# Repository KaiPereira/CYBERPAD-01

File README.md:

# CYBERPAD-01 - Cyberpunk Inspired Macropad

The CYBERPAD-01 is a cyberpunk inspired macropad with 3 keys, a rotary encoder, and a whole lotta silkscreen and neopixels. It uses KMK firmware and was meant to serve as a learning opportunity for PCB's, CAD and rendering. 
## Custom Features
- Custom lasercut acrylic top panel
- EC11 Rotary Encoder for anything really
- 3 Keys to program to your heart's content
- 14 SK6812 MINI-E LEDs for backlight and and diffusion
- Cyberpunk inspired case for maximum aesthetic
-  Exposed PCB design with custom silkscreen cuz it's sick
## CAD Design

I used Onshape to design all of my parts. The laser cut acrylic panel is held together using minimalist bolts and spacers attached to the top plate. The actual case is designed so that everything can fit together seamlessly without using any screws or bolts for minimalism and aesthetics while still being secure.

It comprises of 4 separate 3D printed parts though, the bottom plate/aesthetic walls, the walls, and the top plate, the rotary encoder knob, with the 5th part being the laser cut acrylic top panel, so it's a bit difficult to print, but manageable. [Onshape Link](https://cad.onshape.com/documents/183c405de5c750134bf8a1de/w/282fa5c96ffeba0ae16f58ec/e/f98acd70bf74a51e29d61d0d?renderMode=0&uiState=6869deede1723828ff557213)
## PCB Design

The PCB was designed using KiCad and then I used Figma and the KiCad image converter for creating the silkscreen layers. I actually imported the case design into KiCad so I could use it as reference for the silkscreen which turned out really well.

## Firmware

The CYBERPAD-01 uses KMK firmware (written in Python) and was relatively straightforward.
- The rotary encoder changes volume
- The keys just act as VIM macro's
- Neopixels to backlight and diffuse any color you want

I'll probably make it a bit more complicated in the future, but I think it's kind of handy to have a macropad for some really complicated VIM stuff.

## Bill of Materials (BOM)

Here's everything you'll need to build the CYBERPAD-01:
- 3x Cherry MX Switches
- 3x Keycaps of your choice (I would personally suggest black ones)
- 14x SK6812 MINI-E LEDs
- 1x EC11 Rotary Encoder
- 1x Seeed XIAO RP2040
- 8x M2 Nut and Bolt, 1.5cm, Low profile top
- 8x M2 Spacers, 3mm diameter, 0.6cm, circular, non-threaded
- 1 Case (3 printed parts)
- 1 Custom Laser Cut Acrylic Panel

## Credits and Help

Thanks to @qcoral and @acornitum for starting highway and reviewing projects. @M0HID and @jamdotjar for helping me with Blender and @cheyao for the firmware starter code and helping me make my first macropad!

Also, thanks so much to [PCBWay](https://www.pcbway.com/) for sponsoring the yellow silkscreen PCB's, they look absolutely amazing and I'd highly suggest checking them out if you need really cool looking PCB's and fast turnaround!

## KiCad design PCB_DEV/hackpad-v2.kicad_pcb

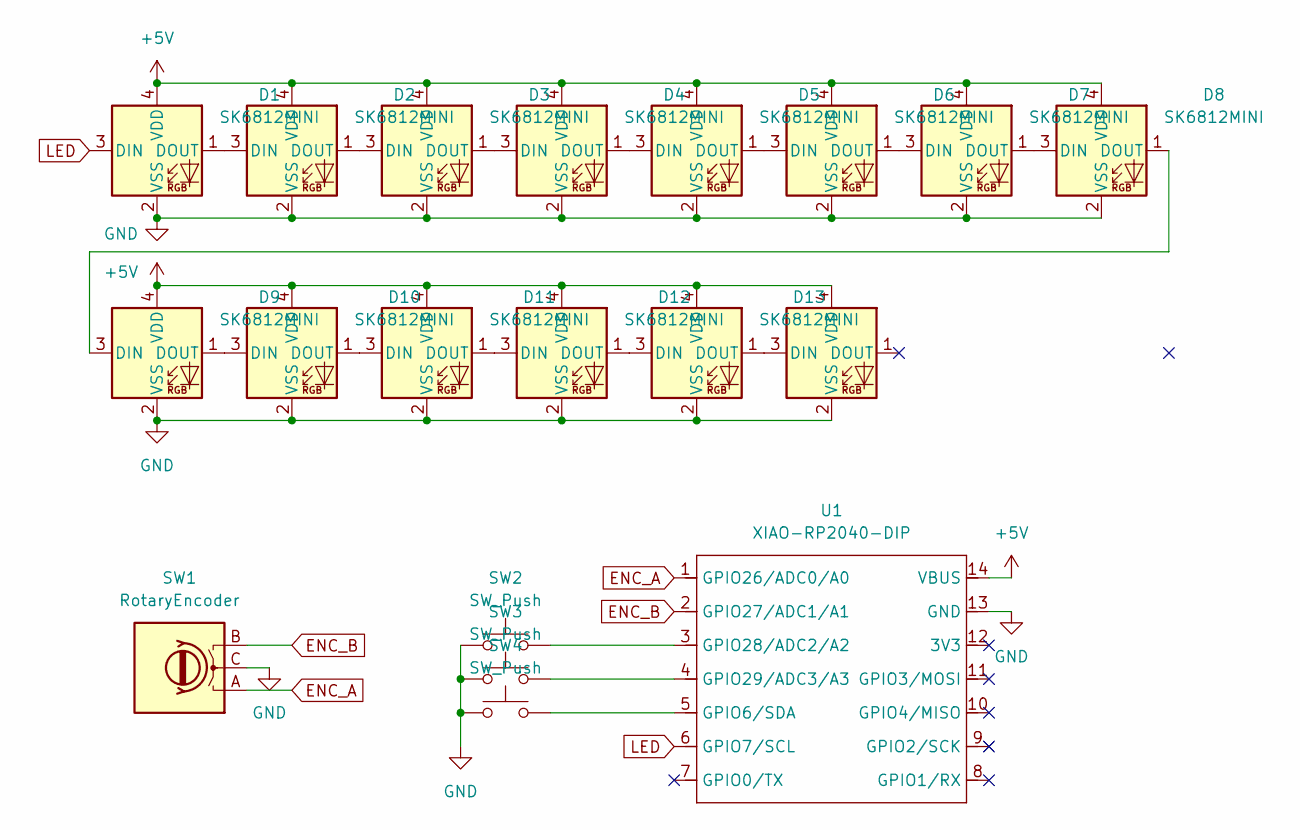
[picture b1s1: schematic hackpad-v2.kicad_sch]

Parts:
D1, D2, D3, D4, D5, D6, D7, D8, D9, D10, D11, D12, D13, D14: SK6812MINI; LED_SK6812MINI_PLCC4_3.5x3.5mm_P1.75mm
SW1: RotaryEncoder; RotaryEncoder_Alps_EC11E-Switch_Vertical_H20mm
SW2, SW3, SW4: SW_Push; SW_Cherry_MX_1.00u_PCB
U1: XIAO-RP2040-DIP

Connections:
+5V: D1.4 (VDD), D2.4 (VDD), D3.4 (VDD), D4.4 (VDD), D5.4 (VDD), D6.4 (VDD), D7.4 (VDD), D8.4 (VDD), D9.4 (VDD), D10.4 (VDD), D11.4 (VDD), D12.4 (VDD), D13.4 (VDD), D14.4 (VDD), U1.14 (VBUS)
ENC_A: SW1.A, U1.1 (GPIO26/ADC0/A0)
ENC_B: SW1.B, U1.2 (GPIO27/ADC1/A1)
GND: D1.2 (VSS), D2.2 (VSS), D3.2 (VSS), D4.2 (VSS), D5.2 (VSS), D6.2 (VSS), D7.2 (VSS), D8.2 (VSS), D9.2 (VSS), D10.2 (VSS), D11.2 (VSS), D12.2 (VSS), D13.2 (VSS), D14.2 (VSS), SW1.C, SW2.1, SW3.1, SW4.1, U1.13 (GND)
LED: D1.3 (DIN), U1.6 (GPIO7/SCL)
unnamed: D1.1 (DOUT), D2.3 (DIN)
unnamed: D2.1 (DOUT), D3.3 (DIN)
unnamed: D3.1 (DOUT), D4.3 (DIN)
unnamed: D4.1 (DOUT), D5.3 (DIN)
unnamed: D5.1 (DOUT), D6.3 (DIN)
unnamed: D6.1 (DOUT), D7.3 (DIN)
unnamed: D7.1 (DOUT), D8.3 (DIN)
unnamed: D8.1 (DOUT), D9.3 (DIN)
unnamed: D9.1 (DOUT), D10.3 (DIN)
unnamed: D10.1 (DOUT), D11.3 (DIN)
unnamed: D11.1 (DOUT), D12.3 (DIN)
unnamed: D12.1 (DOUT), D13.3 (DIN)
unnamed: D13.1 (DOUT), D14.3 (DIN)
unnamed: SW4.2, U1.5 (GPIO6/SDA)
unnamed: SW2.2, U1.3 (GPIO28/ADC2/A2)
unnamed: SW3.2, U1.4 (GPIO29/ADC3/A3)

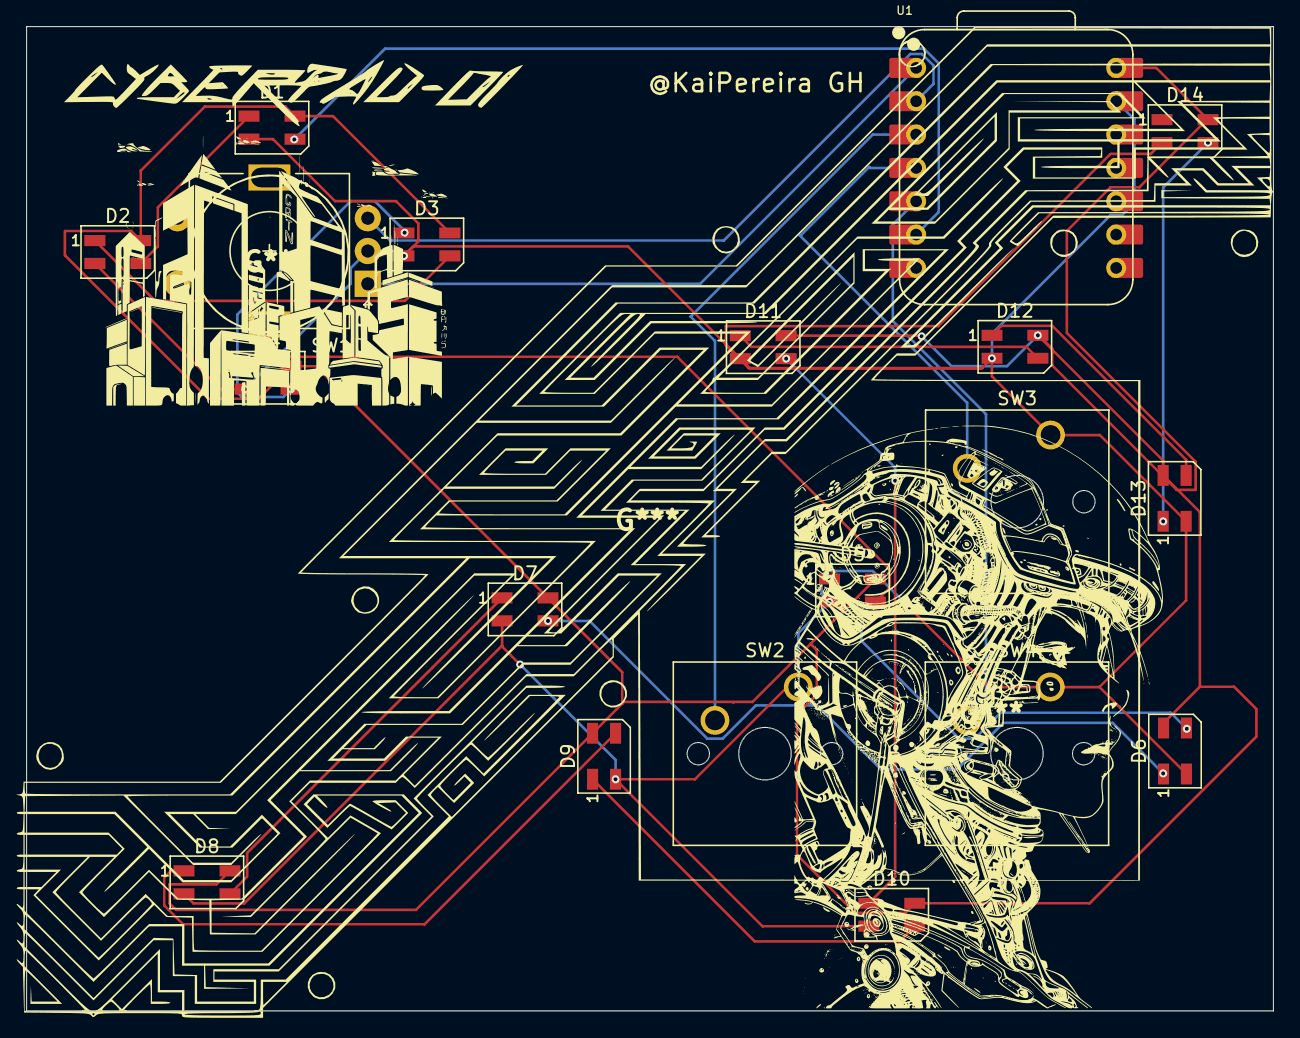
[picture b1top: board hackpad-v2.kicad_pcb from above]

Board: 2 copper layers, 95.0 x 75.0 mm, 19 parts (0 on the bottom side), 21 nets.

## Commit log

2025-07-03 added all my files so far
2025-07-03 adding firmware
2025-07-05 some more blender stuff
2025-07-05 just moving soem stuff
2025-07-05 updated blender file
2025-07-05 MOHID IS A GENIUS, FOLLOW HIM PLLSLS @M0HID
2025-07-05 saving
2025-07-05 readme and journal
2025-07-05 readme upd
2025-07-05 upd readme again
2025-07-06 some readme stuff
2025-07-06 better main photo's
2025-07-06 added my bill of materials
2025-07-06 added stuff to readme
2025-07-06 readme improvements
2025-07-06 some more journal stuff, still need to run my vim macro to convert obsidian images to github images
2025-07-06 all the journal and production files
2025-07-06 fixed all images in journal.md
2025-07-06 added some stuff to the treadme
2025-07-06 added stuff to journal
2025-07-06 ADDED BOM
2025-07-08 update journal for highway site
2025-08-07 updating journal
2025-08-13 updated the readme with build temporarily
2025-08-13 updated link
2025-09-12 fixed images
2025-12-18 Added real photo in!
2025-12-18 Removing build process!
